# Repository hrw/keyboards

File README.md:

Here I plan to keep information about keyboards I worked on.

# [Alicja v1](alicja-v1/)

Yet another fork of fork of fork with Alice like layout.

[Blog post](https://marcin.juszkiewicz.com.pl/2025/03/09/i-built-my-first-mechanical-keyboard/)

Keyboard features:

- Handwired
- two encoders
- UltimatePico as MCU
- QMK with VIA.

Built only one copy. Dead keyboard, dead project.

# [Alicja v2](alicja-v2/)

[Blog post](https://marcin.juszkiewicz.com.pl/2026/07/29/new-keyboard-alicja-v2/)

Keyboard features:

- PCB
- hotswap
- encoder
- 5-way switch
- stabilisers
- RP2040 Stamp as MCU
- QMK with VIA
- connector with spare GPIO lines and power

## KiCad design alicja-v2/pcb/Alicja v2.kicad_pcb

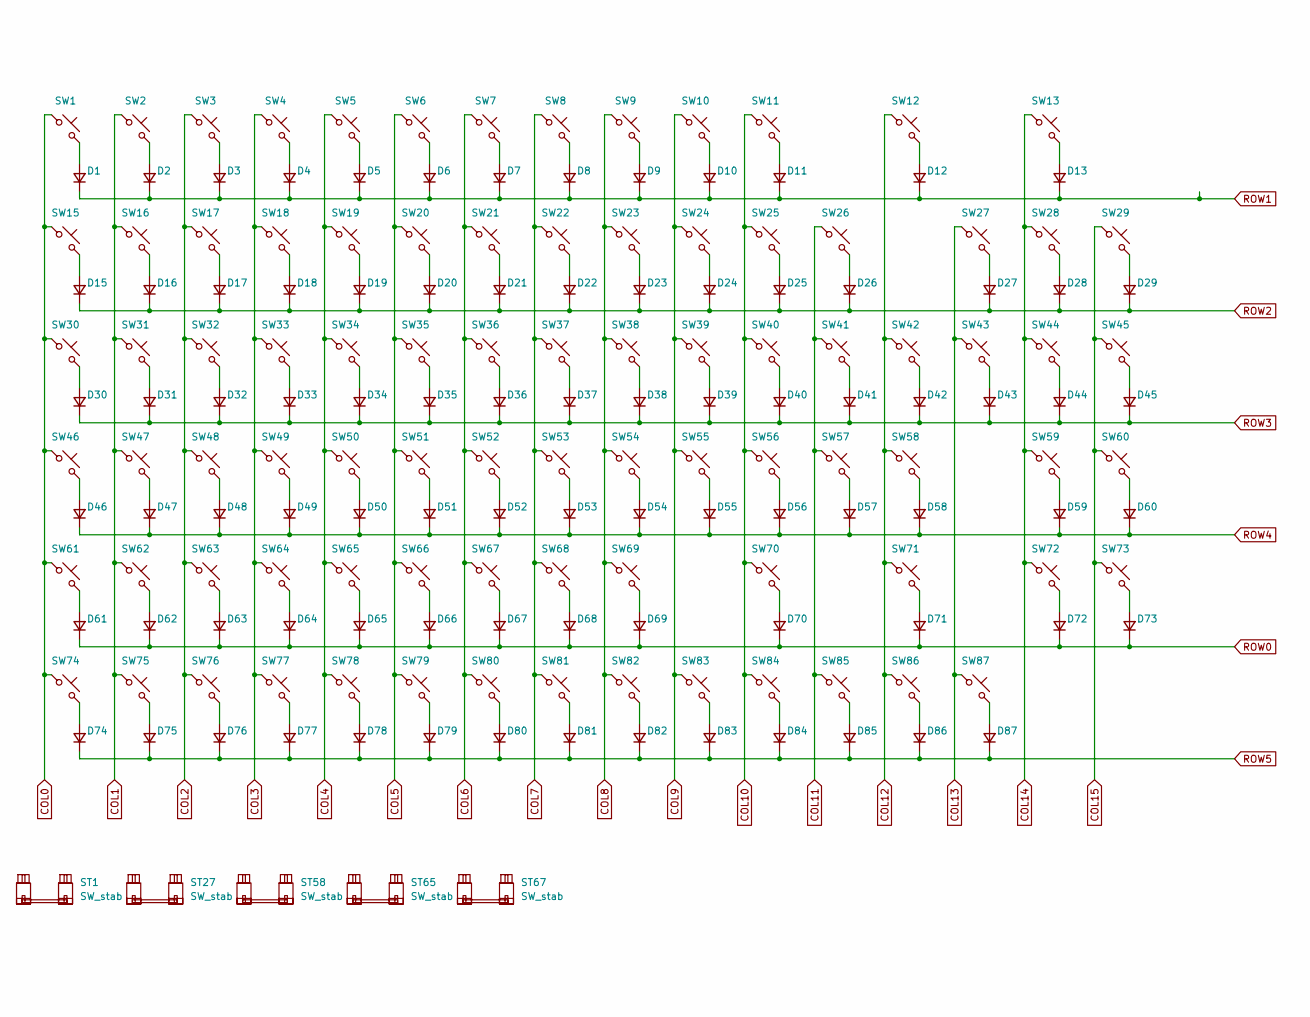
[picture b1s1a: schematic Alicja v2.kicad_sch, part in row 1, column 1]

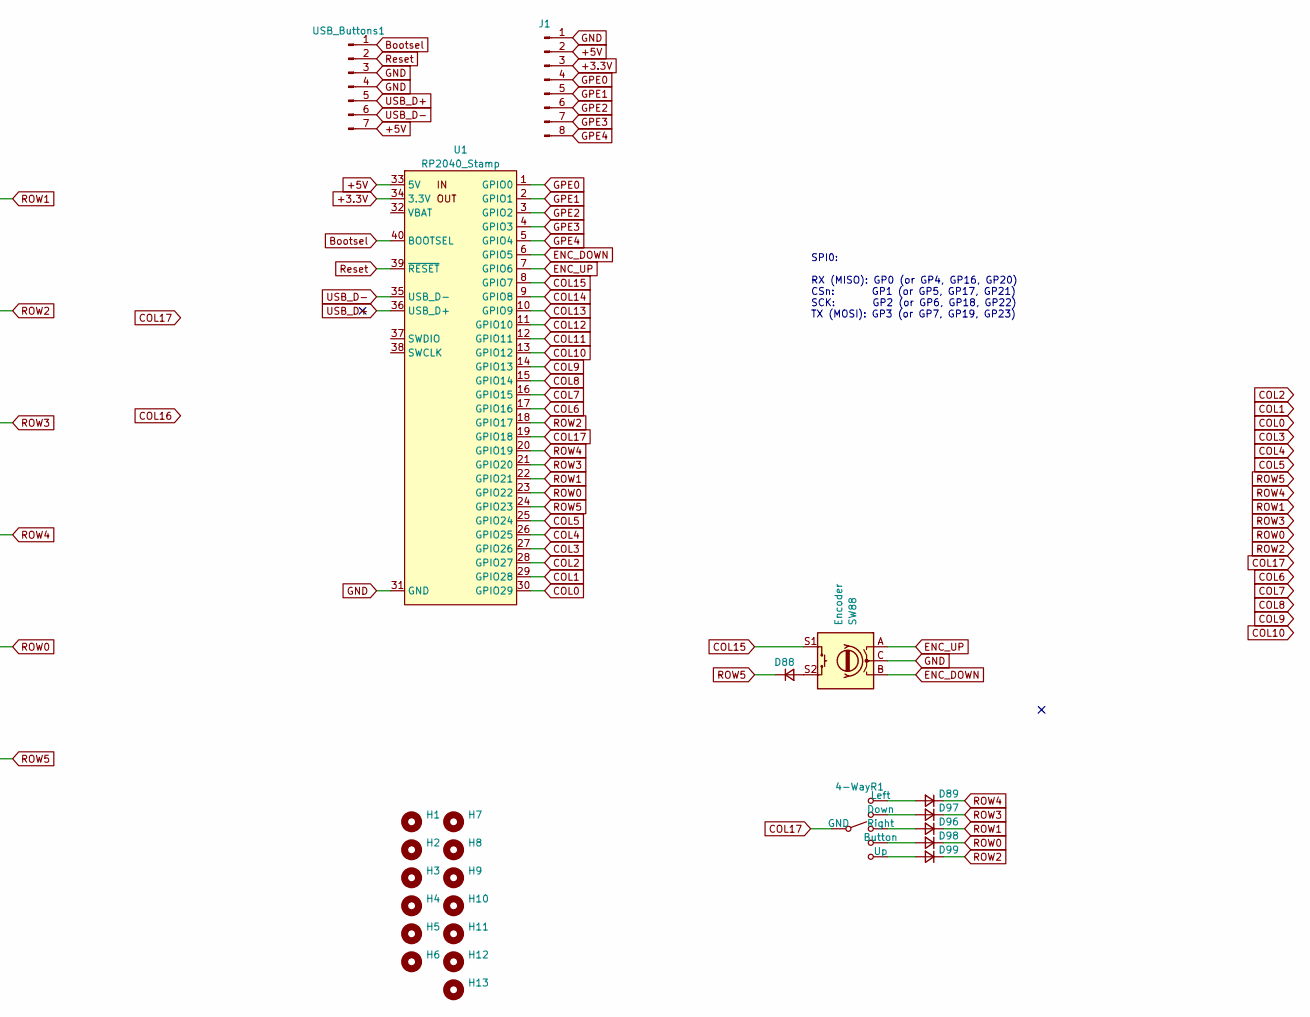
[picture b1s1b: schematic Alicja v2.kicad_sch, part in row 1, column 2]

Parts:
4-WayR1: 4-Way Ali
D1, D2, D3, D4, D5, D6, D7, D8, D9, D10, D11, D12, D13, D15, D16, D17, D18, D19, D20, D21, D22, D23, D24, D25, D26, D27, D28, D29, D30, D31, D32, D33, D34, D35, D36, D37, D38, D39, D40, D41, D42, D43, D44, D45, D46, D47, D48, D49, D50, D51, D52, D53, D54, D55, D56, D57, D58, D59, D60, D61, D62, D63, D64, D65, D66, D67, D68, D69, D70, D71, D72, D73, D74, D75, D76, D77, D78, D79, D80, D81, D82, D83, D84, D85, D86, D87, D88, D89, D96, D97, D98, D99: D; D_1206_3216Metric_Pad1.42x1.75mm_HandSolder
H1, H2, H3, H4, H5, H6, H7, H8, H9, H10, H11, H12, H13: MountingHole; MountingHole_2.5mm
J1: Conn_01x08_Pin; JST_XH_B8B-XH-AM_1x08_P2.50mm_Vertical_SMD
ST1, ST27, ST58, ST65, ST67: SW_stab; Stabilizer_Cherry_MX_2.00u
SW1, SW27: SW_Push; SW_Hotswap_Kailh_MX_2.25u
SW2, SW3, SW4, SW5, SW6, SW7, SW8, SW9, SW10, SW11, SW13, SW16, SW17, SW18, SW19, SW20, SW21, SW22, SW23, SW24, SW25, SW26, SW28, SW29, SW31, SW32, SW33, SW34, SW35, SW36, SW37, SW38, SW39, SW40, SW41, SW42, SW44, SW45, SW46, SW47, SW48, SW49, SW50, SW51, SW52, SW53, SW54, SW55, SW56, SW57, SW59, SW60, SW63, SW66, SW68, SW71, SW72, SW73, SW74, SW75, SW76, SW77, SW78, SW79, SW80, SW81, SW82, SW83, SW84, SW85, SW86, SW87: SW_Push; SW_Hotswap_Kailh_MX_1.00u
SW12: SW_Push; SW_Hotswap_Kailh_MX_1.75u
SW15: SW_Push; SW_Hotswap_Kailh_MX_1.25u
SW30, SW43, SW61, SW62, SW64, SW69, SW70: SW_Push; SW_Hotswap_Kailh_MX_1.50u
SW58, SW65: SW_Push; SW_Hotswap_Kailh_MX_2.00u
SW67: SW_Push; SW_Hotswap_Kailh_MX_2.75u
SW88: Encoder; RotaryEncoder_Alps_EC11E-Switch_Vertical_H20mm_SMD
U1: RP2040_Stamp; RP2xxx_Stamp_SMD
USB_Buttons1: Conn_01x07_Pin; JST_XH_B8B-XH-AM_1x07_P2.50mm_Vertical_SMD

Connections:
+3.3V: J1.3, U1.34 (3.3V)
+5V: J1.2, U1.33 (5V), USB_Buttons1.7
Bootsel: U1.40 (BOOTSEL), USB_Buttons1.1
COL0: SW1.1, SW15.1, SW30.1, SW46.1, SW61.1, SW74.1, U1.30 (GPIO29)
COL1: SW2.1, SW16.1, SW31.1, SW47.1, SW62.1, SW75.1, U1.29 (GPIO28)
COL2: SW3.1, SW17.1, SW32.1, SW48.1, SW63.1, SW76.1, U1.28 (GPIO27)
COL3: SW4.1, SW18.1, SW33.1, SW49.1, SW64.1, SW77.1, U1.27 (GPIO26)
COL4: SW5.1, SW19.1, SW34.1, SW50.1, SW65.1, SW78.1, U1.26 (GPIO25)
COL5: SW6.1, SW20.1, SW35.1, SW51.1, SW66.1, SW79.1, U1.25 (GPIO24)
COL6: SW7.1, SW21.1, SW36.1, SW52.1, SW67.1, SW80.1, U1.17 (GPIO16)
COL7: SW8.1, SW22.1, SW37.1, SW53.1, SW68.1, SW81.1, U1.16 (GPIO15)
COL8: SW9.1, SW23.1, SW38.1, SW54.1, SW69.1, SW82.1, U1.15 (GPIO14)
COL9: SW10.1, SW24.1, SW39.1, SW55.1, SW83.1, U1.14 (GPIO13)
COL10: SW11.1, SW25.1, SW40.1, SW56.1, SW70.1, SW84.1, U1.13 (GPIO12)
COL11: SW26.1, SW41.1, SW57.1, SW85.1, U1.12 (GPIO11)
COL12: SW12.1, SW42.1, SW58.1, SW71.1, SW86.1, U1.11 (GPIO10)
COL13: SW27.1, SW43.1, SW87.1, U1.10 (GPIO9)
COL14: SW13.1, SW28.1, SW44.1, SW59.1, SW72.1, U1.9 (GPIO8)
COL15: SW29.1, SW45.1, SW60.1, SW73.1, SW88.S1, U1.8 (GPIO7)
COL17: 4-WayR1.6 (GND), U1.19 (GPIO18)
ENC_DOWN: SW88.B, U1.6 (GPIO5)
ENC_UP: SW88.A, U1.7 (GPIO6)
GND: J1.1, SW88.C, U1.31 (GND), USB_Buttons1.3, USB_Buttons1.4
GPE0: J1.4, U1.1 (GPIO0)
GPE1: J1.5, U1.2 (GPIO1)
GPE2: J1.6, U1.3 (GPIO2)
GPE3: J1.7, U1.4 (GPIO3)
GPE4: J1.8, U1.5 (GPIO4)
unnamed: 4-WayR1.4 (Button), D98.2 (A)
unnamed: 4-WayR1.2 (Down), D97.2 (A)
unnamed: 4-WayR1.1 (Left), D89.2 (A)
unnamed: 4-WayR1.3 (Right), D96.2 (A)
unnamed: 4-WayR1.5 (Up), D99.2 (A)
unnamed: D1.2 (A), SW1.2
unnamed: D2.2 (A), SW2.2
unnamed: D3.2 (A), SW3.2
unnamed: D4.2 (A), SW4.2
unnamed: D5.2 (A), SW5.2
unnamed: D6.2 (A), SW6.2
unnamed: D7.2 (A), SW7.2
unnamed: D8.2 (A), SW8.2
unnamed: D9.2 (A), SW9.2
unnamed: D10.2 (A), SW10.2
unnamed: D11.2 (A), SW11.2
unnamed: D12.2 (A), SW12.2
unnamed: D13.2 (A), SW13.2
unnamed: D15.2 (A), SW15.2
unnamed: D16.2 (A), SW16.2
unnamed: D17.2 (A), SW17.2
unnamed: D18.2 (A), SW18.2
unnamed: D19.2 (A), SW19.2
unnamed: D20.2 (A), SW20.2
unnamed: D21.2 (A), SW21.2
unnamed: D22.2 (A), SW22.2
unnamed: D23.2 (A), SW23.2
unnamed: D24.2 (A), SW24.2
unnamed: D25.2 (A), SW25.2
unnamed: D26.2 (A), SW26.2
unnamed: D27.2 (A), SW27.2
unnamed: D28.2 (A), SW28.2
unnamed: D29.2 (A), SW29.2
unnamed: D30.2 (A), SW30.2
unnamed: D31.2 (A), SW31.2
unnamed: D32.2 (A), SW32.2
unnamed: D33.2 (A), SW33.2
unnamed: D34.2 (A), SW34.2
unnamed: D35.2 (A), SW35.2
unnamed: D36.2 (A), SW36.2
unnamed: D37.2 (A), SW37.2
unnamed: D38.2 (A), SW38.2
unnamed: D39.2 (A), SW39.2
unnamed: D40.2 (A), SW40.2
unnamed: D41.2 (A), SW41.2
unnamed: D42.2 (A), SW42.2
unnamed: D43.2 (A), SW43.2
unnamed: D44.2 (A), SW44.2
unnamed: D45.2 (A), SW45.2
unnamed: D46.2 (A), SW46.2
unnamed: D47.2 (A), SW47.2
unnamed: D48.2 (A), SW48.2
unnamed: D49.2 (A), SW49.2
unnamed: D50.2 (A), SW50.2
unnamed: D51.2 (A), SW51.2
unnamed: D52.2 (A), SW52.2
unnamed: D53.2 (A), SW53.2
unnamed: D54.2 (A), SW54.2
unnamed: D55.2 (A), SW55.2
unnamed: D56.2 (A), SW56.2
unnamed: D57.2 (A), SW57.2
unnamed: D58.2 (A), SW58.2
unnamed: D59.2 (A), SW59.2
unnamed: D60.2 (A), SW60.2
unnamed: D61.2 (A), SW61.2
unnamed: D62.2 (A), SW62.2
unnamed: D63.2 (A), SW63.2
unnamed: D64.2 (A), SW64.2
unnamed: D65.2 (A), SW65.2
unnamed: D66.2 (A), SW66.2
unnamed: D67.2 (A), SW67.2
unnamed: D68.2 (A), SW68.2
unnamed: D69.2 (A), SW69.2
unnamed: D70.2 (A), SW70.2
unnamed: D71.2 (A), SW71.2
unnamed: D72.2 (A), SW72.2
unnamed: D73.2 (A), SW73.2
unnamed: D74.2 (A), SW74.2
unnamed: D75.2 (A), SW75.2
unnamed: D76.2 (A), SW76.2
unnamed: D77.2 (A), SW77.2
unnamed: D78.2 (A), SW78.2
unnamed: D79.2 (A), SW79.2
unnamed: D80.2 (A), SW80.2
unnamed: D81.2 (A), SW81.2
unnamed: D82.2 (A), SW82.2
unnamed: D83.2 (A), SW83.2
unnamed: D84.2 (A), SW84.2
unnamed: D85.2 (A), SW85.2
unnamed: D86.2 (A), SW86.2
unnamed: D87.2 (A), SW87.2
unnamed: D88.2 (A), SW88.S2
ROW0: D61.1 (K), D62.1 (K), D63.1 (K), D64.1 (K), D65.1 (K), D66.1 (K), D67.1 (K), D68.1 (K), D69.1 (K), D70.1 (K), D71.1 (K), D72.1 (K), D73.1 (K), D98.1 (K), U1.23 (GPIO22)
ROW1: D1.1 (K), D2.1 (K), D3.1 (K), D4.1 (K), D5.1 (K), D6.1 (K), D7.1 (K), D8.1 (K), D9.1 (K), D10.1 (K), D11.1 (K), D12.1 (K), D13.1 (K), D96.1 (K), U1.22 (GPIO21)
ROW2: D15.1 (K), D16.1 (K), D17.1 (K), D18.1 (K), D19.1 (K), D20.1 (K), D21.1 (K), D22.1 (K), D23.1 (K), D24.1 (K), D25.1 (K), D26.1 (K), D27.1 (K), D28.1 (K), D29.1 (K), D99.1 (K), U1.18 (GPIO17)
ROW3: D30.1 (K), D31.1 (K), D32.1 (K), D33.1 (K), D34.1 (K), D35.1 (K), D36.1 (K), D37.1 (K), D38.1 (K), D39.1 (K), D40.1 (K), D41.1 (K), D42.1 (K), D43.1 (K), D44.1 (K), D45.1 (K), D97.1 (K), U1.21 (GPIO20)
ROW4: D46.1 (K), D47.1 (K), D48.1 (K), D49.1 (K), D50.1 (K), D51.1 (K), D52.1 (K), D53.1 (K), D54.1 (K), D55.1 (K), D56.1 (K), D57.1 (K), D58.1 (K), D59.1 (K), D60.1 (K), D89.1 (K), U1.20 (GPIO19)
ROW5: D74.1 (K), D75.1 (K), D76.1 (K), D77.1 (K), D78.1 (K), D79.1 (K), D80.1 (K), D81.1 (K), D82.1 (K), D83.1 (K), D84.1 (K), D85.1 (K), D86.1 (K), D87.1 (K), D88.1 (K), U1.24 (GPIO23)
Reset: U1.39 (~RESET), USB_Buttons1.2
USB_D+: U1.36 (USB_D+), USB_Buttons1.5
USB_D-: U1.35 (USB_D-), USB_Buttons1.6

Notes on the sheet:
SPI0: RX (MISO): GP0 (or GP4, GP16, GP20) CSn: GP1 (or GP5, GP17, GP21) SCK: GP2 (or GP6, GP18, GP22) TX (MOSI): GP3 (or GP7, GP19, GP23)

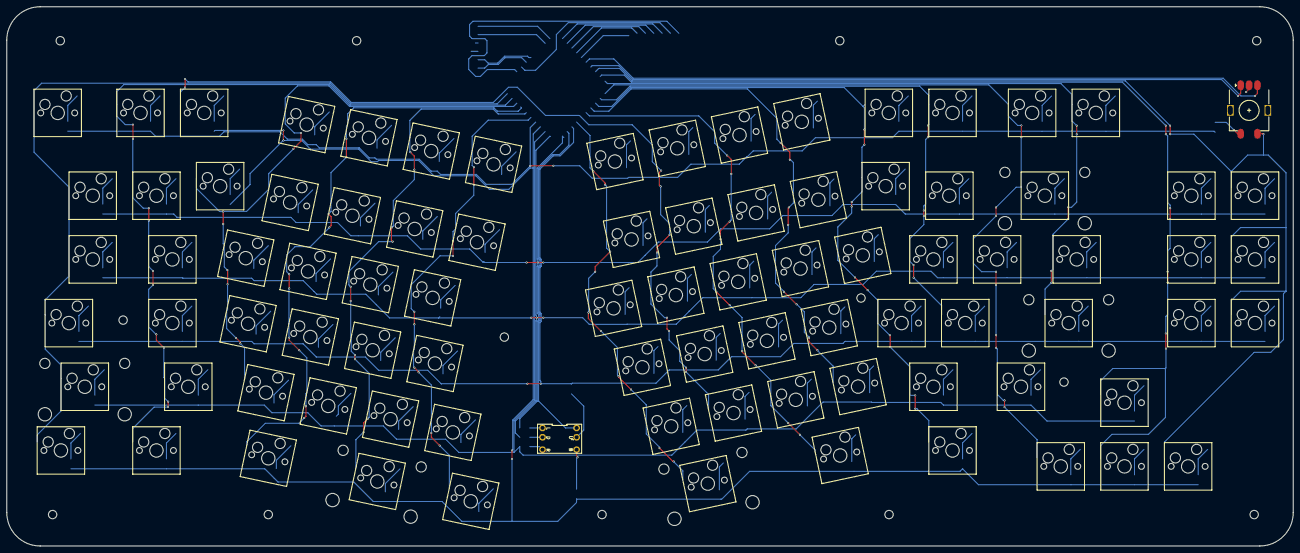
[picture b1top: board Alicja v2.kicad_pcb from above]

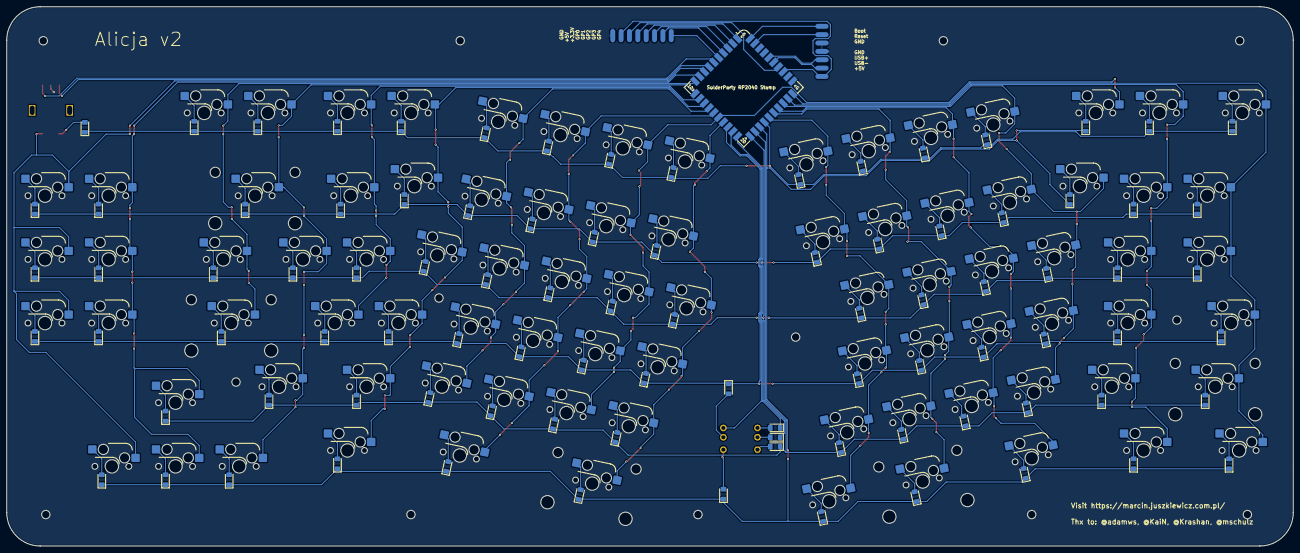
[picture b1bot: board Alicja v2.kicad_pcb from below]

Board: 2 copper layers, 384.8 x 161.3 mm, 201 parts (94 on the bottom side), 129 nets.

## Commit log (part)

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2025-03-31 alicja: add photo of current prototype
2025-03-31 alicja: added photo of bottom
2025-03-31 alicja: add README
2025-03-31 alicja: mention CapsLock mapping
2025-03-31 alicja: keymap for VIA
    Layout which I use in prototype
2025-03-31 alicja: add QMK firmware files
    Enough to get it built, does not contain keymap from VIA
2025-03-31 alicja: add JSON matrix file for VIA
    This file is needed to be able to remap keys using VIA website.
    I use USB vid/pid from Adelheid keyboard but with own matrix so this
    file is required.
2025-03-31 alicja: added link to blog post
2025-03-31 alicja: updated README
    Changes done to Adelheid + KLE link.
2025-03-31 alicja: move keymap to JSON
    This would allow to use https://config.qmk.fm/ website to edit keymap.
2025-03-31 alicja: set URL in keyboard json
    Let it point to Github repo for now.
2025-03-31 alicja: disable mousekeys
2025-03-31 alicja: update key name for Del
2025-03-31 alicja: reformat C source
